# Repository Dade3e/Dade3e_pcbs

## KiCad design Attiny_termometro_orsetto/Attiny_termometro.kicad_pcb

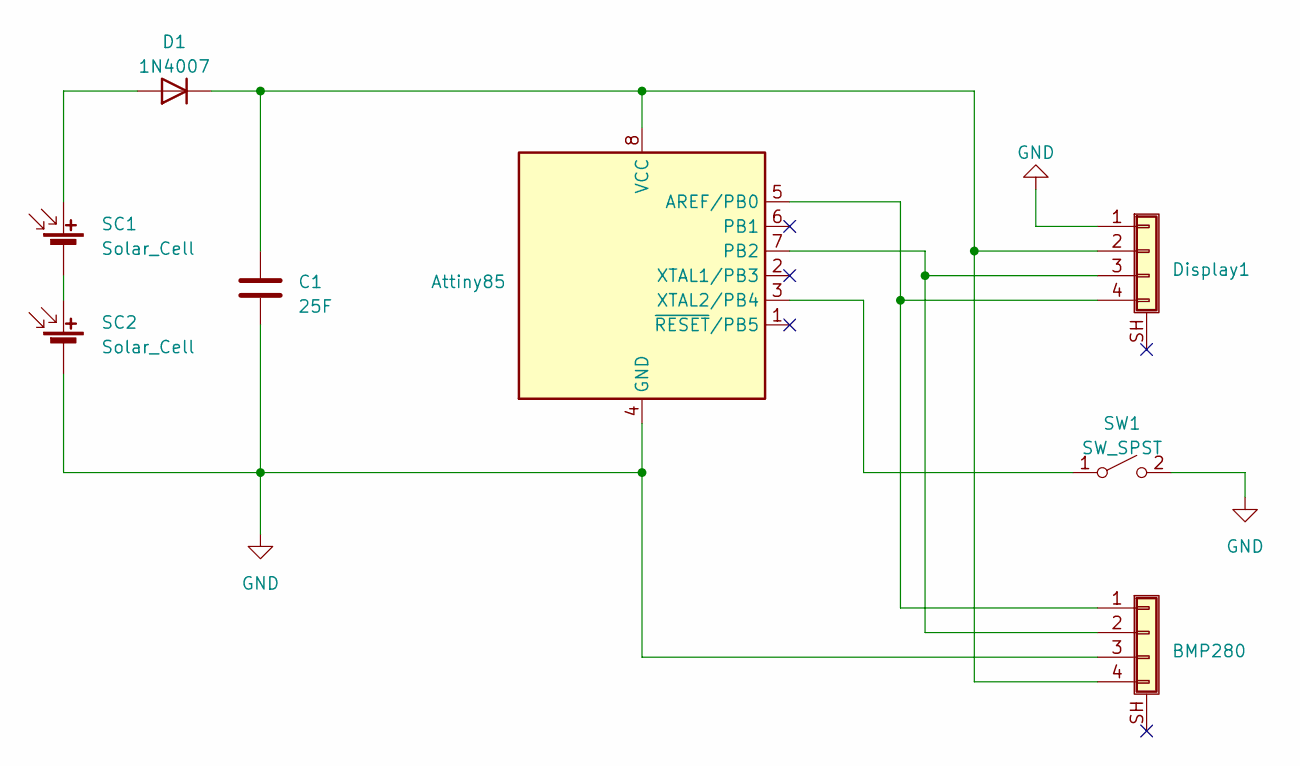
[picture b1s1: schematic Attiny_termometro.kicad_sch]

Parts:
Attiny85: ATtiny85-20P; DIP-8_W7.62mm_Socket
BMP280: Conn_01x04_Shielded; PinSocket_1x04_P2.54mm_Vertical
C1: 25F; CP_Radial_D8.0mm_P3.80mm
D1: 1N4007; D_DO-41_SOD81_P10.16mm_Horizontal
Display1: Conn_01x04_Shielded; Display_i2c_128x32
SC1, SC2: Solar_Cell; solar_panel
SW1: SW_SPST; SW_PUSH_6mm_H8mm

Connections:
GND: Attiny85.4 (GND), BMP280.3, C1.2, Display1.1, SC2.2 (-), SW1.2 (B)
unnamed: Attiny85.5 (AREF/PB0), BMP280.1, Display1.4
unnamed: Attiny85.7 (PB2), BMP280.2, Display1.3
unnamed: Attiny85.8 (VCC), BMP280.4, C1.1, D1.1 (K), Display1.2
unnamed: Attiny85.3 (XTAL2/PB4), SW1.1 (A)
unnamed: D1.2 (A), SC1.1 (+)
unnamed: SC1.2 (-), SC2.1 (+)

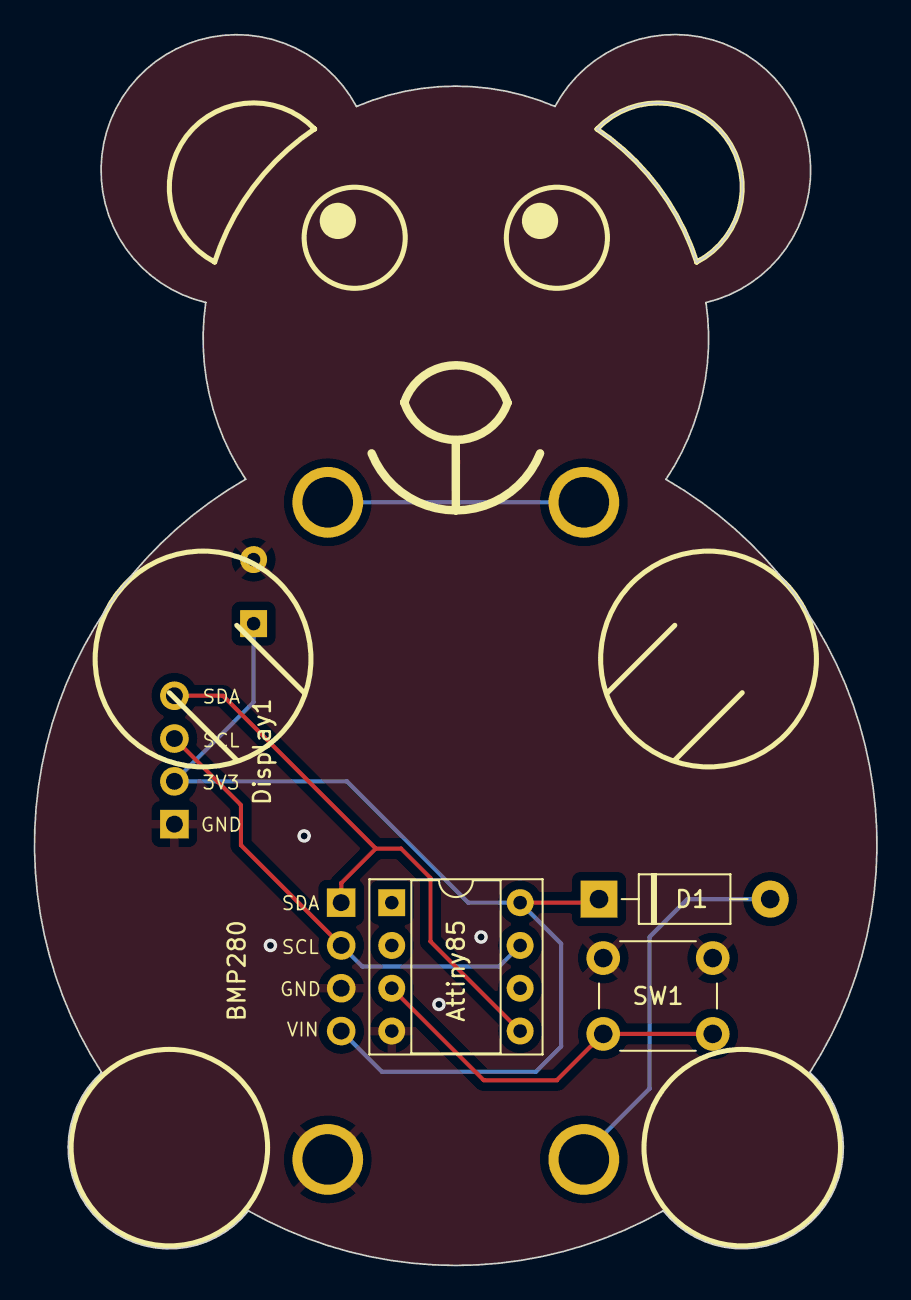
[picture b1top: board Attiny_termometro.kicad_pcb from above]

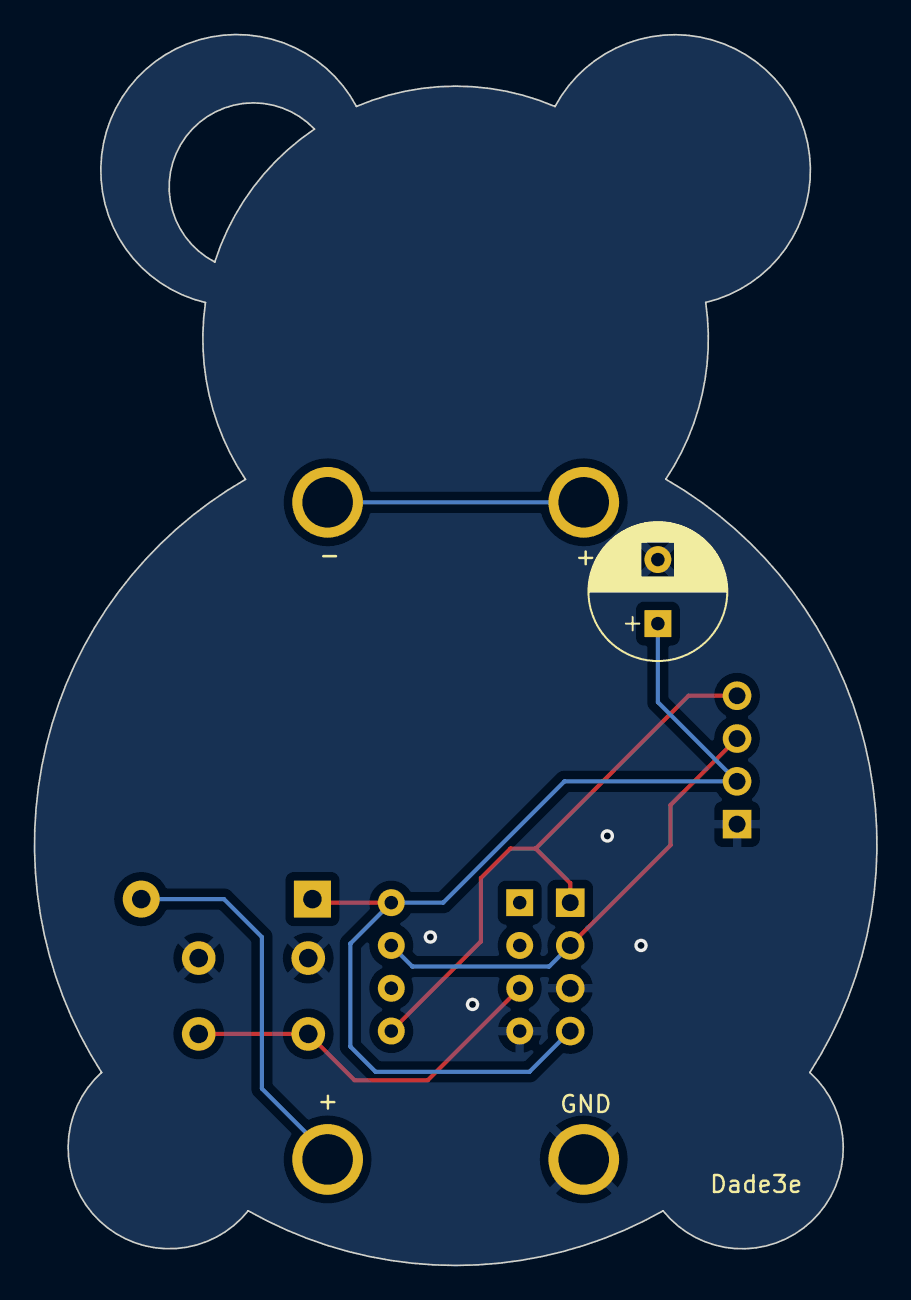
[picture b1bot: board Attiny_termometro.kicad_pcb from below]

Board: 2 copper layers, 50.0 x 73.1 mm, 8 parts (3 on the bottom side), 7 nets.

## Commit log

2023-05-30 Attiny BMP280
